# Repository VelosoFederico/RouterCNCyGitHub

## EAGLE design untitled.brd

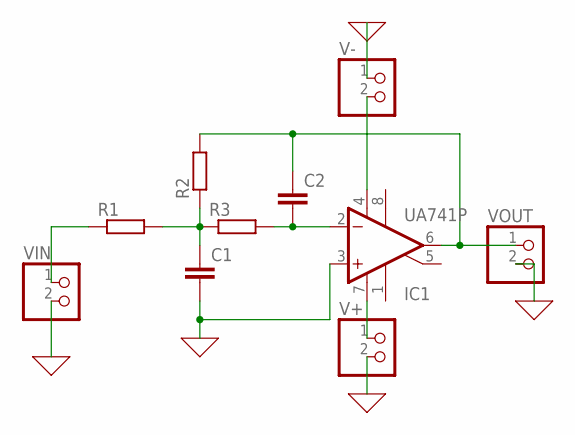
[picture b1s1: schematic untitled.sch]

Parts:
C1, C2: C-EU025-025X050; C025-025X050
IC1: UA741P; DIL08
R1, R2, R3: R-EU_0411/3V; 0411V
V+: PINHD-1X2; 1X02
V-: PINHD-1X2; 1X02
VIN: PINHD-1X2; 1X02
VOUT: PINHD-1X2; 1X02

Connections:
0: C1.2, IC1.3 (+IN), V+.2, V-.1, VIN.2, VOUT.2
unnamed: C1.1, R1.2, R2.1, R3.1
unnamed: IC1.7 (V+), V+.1
unnamed: IC1.4 (V-), V-.2
unnamed: C2.1, IC1.6 (OUT), R2.2, VOUT.1
unnamed: C2.2, IC1.2 (-IN), R3.2
unnamed: R1.1, VIN.1

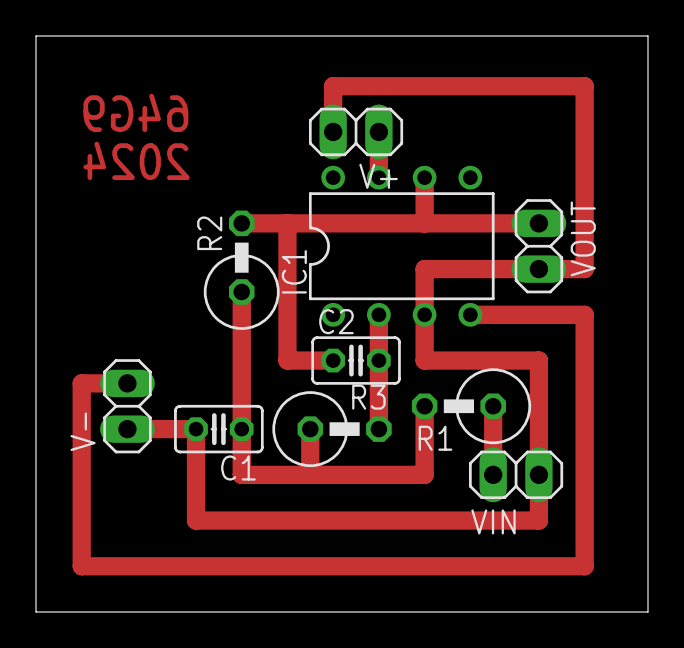
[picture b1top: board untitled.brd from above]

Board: 2 copper layers, 34.0 x 32.0 mm, 10 parts (0 on the bottom side), 7 nets.
